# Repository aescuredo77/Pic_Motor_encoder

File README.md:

# Pic_Motor_encoder
The  I2C ServoMotor can serve different purposes, for example, like servo that we need positioning and hold, while the diffrobot we are interested in speed. 

 **ServoMotor detail of the interior circuit** 

## Description ##
The servomotor consists of a controller board with a PIC16f1503 and a LB1938FA driver, which drive a Pololu &quot;Micro-metal-gearmotors&quot; type reduction motor. The reduction of the motors is based on the need for example:

- 100: 1, 130 rpm
- 298:1, 45 rpm

The microcontroller communicates through I2C, which allows us to connect 127 nodes in series. There will not be so many in our applications, we have asked for LP motors, Low power because they have a low consumption that allows us to connect them in series.

The I2c address will depend on the application that we are going to make, it should not be a problem to change it depending on the needs, but we are going to give a few premises. The I2C addresses are defined by 7 bits, the least significant bit tells us if it is writing or reading, so we will give a couple of addresses, the first is the one recorded in the pic, and the other is the one we will use in the Arduino / teensy to communicate. Always in Hexadecinal.

| Name            | Mode     | address | address Arduino |
| --------------- | -------- | --------| ----------------|
|Servo_Motor_Left |   speed  |   0x22  |       0x11      |
|Servo_Motor_Rigt |   speed  |   0x20  |       0x10      |
|Gripper          | position |   0x10  |       0x08      |
|Servo_base       | position |   0x30  |       0x18      |
|Servo_left       | position |   0x32  |       0x19      |
|Servo_right      | position |   0x34  |       0x1A      |

The 12 pulses per turn encoder must be multiplied by the reduction of the motor to obtain the pulses per turn that the motor will give.For example in the case of reduction 100:1 the servoMotor needs 1200 pulses to complete a lap.

## Boards and Schematics ##

**ServoMotor board in Eagle**

**ServoMotor schematic in Eagle** 

## Electronics  

[PIC16F1503](http://ww1.microchip.com/downloads/en/DeviceDoc/40001607D.pdf) 14 pin Flash, 8 bit microcontroller, 16Mhz internal Oscillator, 2Kwords linear program, 128 data SDRAM, 8 Analog to Digital converter at 10 bit resolution, 4 PWM, 3 Timers, I2C/SPI.

The driver is [LB1938FA](https://www.dropbox.com/s/l5har1ai8nknbxs/LB1938FA.pdf?dl=0), It is a driver configured in H-bridge that allows us to control the motor in speed and direction with only two inputs. Analyzing the driver that the DFRobot servomotors carry, the L9110S looks for alternatives because the aforementioned driver is a little out of print or is only sold on pages of doubtful reliability.

 **LB1938FA is the cousin of the L9110S carried by Dfrobotics servos.** 

 **Detail of the motor control board** 

#### Note: For a Diffrobot model the motor on the right is mounted in the opposite direction from that on the left. The micrometal motor gearboxes are not symmetrical. In this way we equalize the mechanical behavior. #### 

If you need more powerful motors or those that require a greater workload, there is a version of these servos with an independent power supply from the motors.

## Sottware ##

The "/Electronics/src/" folder contains the versions of the PIC program for operating the  left/right servoMotor. Different programs are needed because the motors are reversed. We can use this program for any application, gripper or servoPosition or continuous servo. 

To use it in both arduino and teensy or similar, a library has been made in c++ that is in the arduino folder.

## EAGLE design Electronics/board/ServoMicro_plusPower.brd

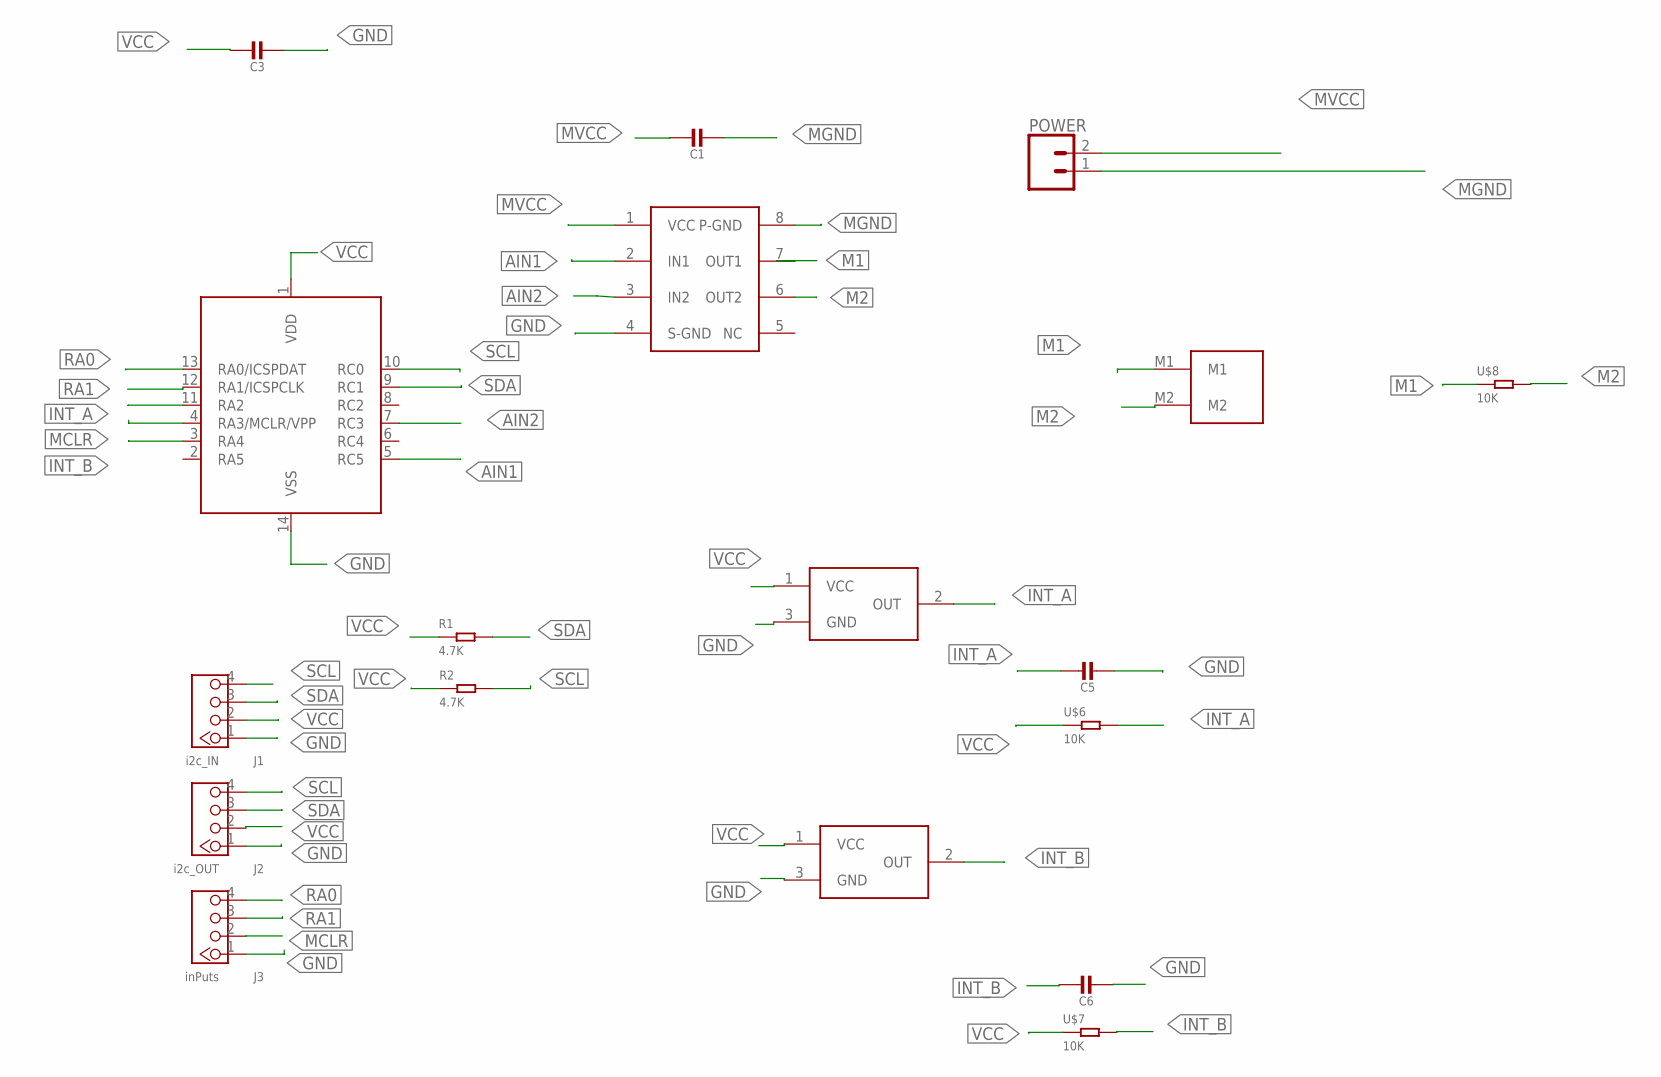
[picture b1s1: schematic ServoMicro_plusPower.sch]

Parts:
C1, C3, C5, C6: CAP_CERAMIC0805-NOOUTLINE; 0805-NO
J1: i2c_IN; HW4-2.0
J2: i2c_OUT; HW4-2.0
J3: inPuts; HW4-2.0
POWER: CONN_02-JST-2-PTH-NO_SILK; JST-2-PTH-NS
R1, R2: 4.7K; R0805
U$1: LB1938DFA_A; MSOP8
U$2, U$3: DRV5021-Q1; SOT-23
U$4: MICRO_MOTOR
U$5: PIC16F1503SOIC; SO-14
U$6, U$7, U$8: 10K; R0805

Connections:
AIN1: U$1.2 (IN1), U$5.5 (RC5)
AIN2: U$1.3 (IN2), U$5.7 (RC3)
GND: C3.2, C5.2, C6.2, J1.1, J2.1, J3.1, U$1.4 (S-GND), U$2.3 (GND), U$3.3 (GND), U$5.14 (VSS)
INT_A: C5.1, U$2.2 (OUT), U$5.11 (RA2), U$6.2
INT_B: C6.1, U$3.2 (OUT), U$5.3 (RA4), U$7.2
M1: U$1.7 (OUT1), U$4.M1, U$8.1
M2: U$1.6 (OUT2), U$4.M2, U$8.2
MCLR: J3.2, U$5.4 (RA3/MCLR/VPP)
MGND: C1.2, POWER.1, U$1.8 (P-GND)
MVCC: C1.1, POWER.2, U$1.1 (VCC)
RA0: J3.4, U$5.13 (RA0/ICSPDAT)
RA1: J3.3, U$5.12 (RA1/ICSPCLK)
SCL: J1.4, J2.4, R2.2, U$5.10 (RC0)
SDA: J1.3, J2.3, R1.2, U$5.9 (RC1)
VCC: C3.1, J1.2, J2.2, R1.1, R2.1, U$2.1 (VCC), U$3.1 (VCC), U$5.1 (VDD), U$6.1, U$7.1

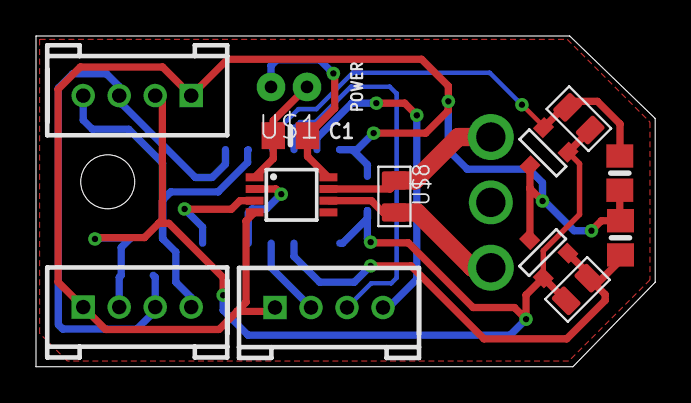
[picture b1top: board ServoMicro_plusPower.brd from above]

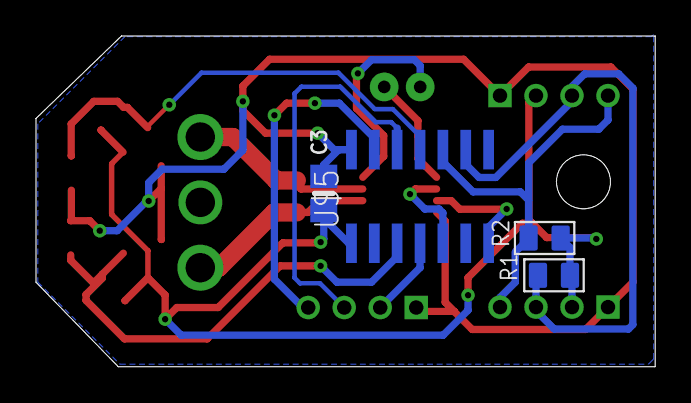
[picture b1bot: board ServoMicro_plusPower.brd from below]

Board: 2 copper layers, 34.4 x 18.4 mm, 18 parts (4 on the bottom side), 15 nets.
